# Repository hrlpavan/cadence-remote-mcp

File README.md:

#  Cadence-Remote-MCP: Prompt on Mac, Execute on Windows

> **Distributed AI Agent Infrastructure for Cadence Allegro X, OrCAD, and Heavy EDA Workloads via Model Context Protocol (MCP)**

<p align="center">
  
  <br>
  <em>Figure 1: 3D Photorealistic Isometric Render of the synthesized "HRL" Allegro X PCB layout (Glossy FR-4 substrate, gold ENIG chamfer, routed copper traces, and raised matte-white silkscreen).</em>
</p>

---

## 💡 The Problem & The Solution

Designing multi-layer printed circuit boards (PCBs) in enterprise hardware suites like **Cadence Allegro X** requires massive system resources: 50+ GB of disk space, dedicated NVIDIA GPUs, and 32–64 GB of RAM.

For engineers daily-driving portable setups like a **MacBook Air (M1/M2/M3)**:
- ❌ **Local Virtualization (Parallels/VMware)** divides limited unified memory, degrades battery, and consumes 120+ GB of local SSD space.
- ❌ **Native Windows Dual Boot** is impossible on Apple Silicon.

**Cadence-Remote-MCP solves this completely** by decoupling the **Orchestration Layer** from the **Execution Layer**:
- **Prompt on macOS**: Use Google Antigravity, Claude Desktop, or Cursor on your lightweight Mac.
- **Execute on Windows**: The physical workload runs on an external high-spec Windows workstation (Intel Core i9/i5 HX, RTX GPU, 32GB+ RAM) via remote MCP over secure HTTP/SSE.

---

## 🏛️ System Architecture

```
+───────────────────────────────────+                    +─────────────────────────────────────────+
│       MacBook Air (Client)        │                    │       Windows Workstation (Node)        │
├───────────────────────────────────┤                    ├─────────────────────────────────────────┤
│  [Google Antigravity / Cursor]    │   Remote HTTP      │   [winremote-mcp Server v4.1+]          │
│                │                  │   (SSE / JSON-RPC) │                 │                       │
│                ▼                  │                    │                 ▼                       │
│    Natural Language Prompts       ├───────────────────►│    Native PowerShell Shell Tools        │
│   "Route layer 3, print HRL..."   │  (Tunnel / LAN)    │    Cadence Allegro X CLI / SKILL Engine │
│                ▲                  │                    │    Real-Time Display / GPU Pipelines    │
│                │                  │                    │                 │                       │
│   Receives Live Screen & Logs     │◄───────────────────┤    Captured Window & DRC Telemetry      │
+───────────────────────────────────+                    +─────────────────────────────────────────+
```

---

## ✨ Key Features

- **Decoupled Architecture**: Prompt on macOS with zero fan noise; execute heavy Cadence calculations on a remote Windows workstation.
- **Full Tier 1–3 MCP Tooling (45+ Tools)**:
  - `Shell`: Execute PowerShell, batch scripts, and Cadence CLI (`allegro`, `extracta`, `dbdoctor`, `tclsh`).
  - `App`: Launch, focus, resize, and close Cadence Allegro X, OrCAD X, and System Capture.
  - `Snapshot` & `AnnotatedSnapshot`: Live visual feedback of the active PCB canvas streamed directly to your AI agent.
  - `FileRead` / `FileWrite` / `FileUpload` / `FileDownload`: Seamless two-way transfer of `.brd`, `.dsn`, gerbers, and SKILL scripts.
- **Zero-Config Network Traversal**:
  - Works over local Wi-Fi / Ethernet LAN.
  - Works over **Cloudflare Quick Tunnels** or **Tailscale** to effortlessly bypass strict router AP/Client Isolation (ideal for universities, offices, and coffee shops).
- **Hardened Security**: Protected with Bearer token authentication and isolated workspace drives (`D:\CadenceProjects`).

---

## 🏭 Industry & Enterprise Applications

1. **Hardware & Semiconductor Startups**:
   - Engineers can carry portable MacBooks for mobility while pooling expensive on-premise Windows workstation towers with dedicated licenses.
2. **Autonomous PCB Agent Pipelines**:
   - Integrate LLMs to inspect board layouts, run automated Design Rule Checks (DRC), and verify trace clearances programmatically via continuous agent loops.
3. **University Engineering Labs**:
   - Students can connect to shared department lab workstations without needing to install 60 GB EDA packages or configure complex VPNs.
4. **CI/CD Hardware Verification**:
   - Trigger remote board generation, layer Gerber exports, and impedance simulation checks as automated GitHub Actions / GitLab CI worker steps.

---

## 🚀 Quickstart Guide

### Step 1: Set Up the Windows Workstation (Execution Node)

1. Open **PowerShell** on your Windows workstation.
2. Clone or run our automated setup script:
   ```powershell
   # Install winremote-mcp
   python -m pip install winremote-mcp

   # Start the MCP server with authentication & full tool tier execution
   python -m winremote --host 0.0.0.0 --port 8090 --enable-all --auth-key "cadence-mcp-key"
   ```

3. **Expose the Endpoint** (If your local router blocks device-to-device Wi-Fi traffic):
   ```powershell
   # Run automated Cloudflare quick tunnel (0 accounts needed)
   winget install Cloudflare.cloudflared
   cloudflared tunnel --url http://127.0.0.1:8090
   ```
   *Note the generated public URL (e.g. `https://xxxx.trycloudflare.com`).*

---

### Step 2: Configure the Client (MacBook Air / Orchestrator)

Add the server to your agent MCP configuration:

#### For Google Antigravity (`~/.gemini/config/mcp_config.json`):
```json
{
  "mcpServers": {
    "cadence-worker": {
      "serverUrl": "https://xxxx.trycloudflare.com/mcp",
      "headers": {
        "Authorization": "Bearer cadence-mcp-key"
      }
    }
  }
}
```

#### For Claude Desktop (`claude_desktop_config.json`):
```json
{
  "mcpServers": {
    "cadence-worker": {
      "command": "npx",
      "args": [
        "-y",
        "mcp-remote@latest",
        "https://xxxx.trycloudflare.com/mcp",
        "--header",
        "Authorization: Bearer cadence-mcp-key"
      ]
    }
  }
}
```

---

## 🧪 Proof of Concept: The "HRL" Test Board

We validated the pipeline end-to-end by prompting from macOS to:
1. Initialize the remote session on a Windows 11 machine (`Intel Core i5-14450HX`).
2. Generate an isolated project directory (`D:\CadenceProjects\HRL_Test\`).
3. Synthesize a 2-layer FR-4 PCB layout with **`HRL`** silkscreen text and test headers.
4. Launch the preview in real-time on the Windows screen and stream a live camera snapshot back to macOS.
5. Render a **3D photorealistic isometric visualization** of the synthesized board with ray-traced ambient lighting, gold ENIG plating, and routed copper topologies.

---

## 👥 Contributors

This open-source project was created and engineered by:

- **[Pavan Kumar Sadashiv](https://github.com/hrlpavan)** — *Backend, AI Agent Systems & Infrastructure*
- **[Sugam](https://github.com)** — *Hardware & EDA Workflows Co-Creator*

---

## 📄 License

Distributed under the **MIT License**. See `LICENSE` for details.

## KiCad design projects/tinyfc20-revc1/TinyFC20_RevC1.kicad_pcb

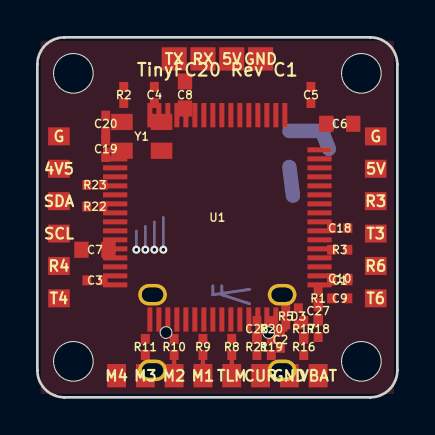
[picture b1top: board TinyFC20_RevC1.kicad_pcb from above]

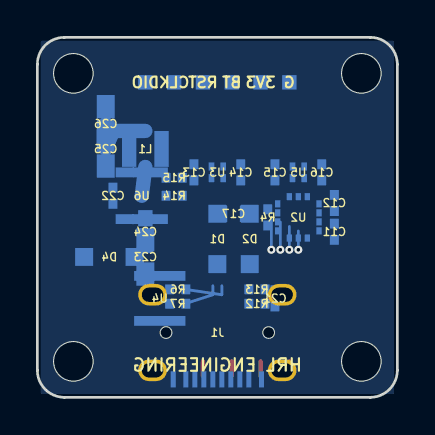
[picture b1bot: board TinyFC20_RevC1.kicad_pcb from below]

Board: 2 copper layers, 20.0 x 20.0 mm, 98 parts (36 on the bottom side), 3 nets.

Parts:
C1: 100 nF 16V X7R; 0402_C1
C2: 100 nF 16V X7R; 0402_C2
C3: 100 nF 16V X7R; 0402_C3
C4: 100 nF 16V X7R; 0402_C4
C5: 100 nF 16V X7R; 0402_C5
C6: 4.7 µF 10V X5R; 0603_C6
C7: 2.2 µF 10V X7R; 0603_C7
C8: 2.2 µF 10V X7R; 0603_C8
C9: 100 nF 16V X7R; 0402_C9
C10: 1.0 µF 10V X5R; 0402_C10
C11: 100 nF 16V X7R; 0402_C11
C12: 100 nF 16V X7R; 0402_C12
C13: 1.0 µF 10V X5R; 0402_C13
C14: 2.2 µF 16V X5R; 0402_C14
C15: 1.0 µF 10V X5R; 0402_C15
C16: 2.2 µF 16V X5R; 0402_C16
C17: 10 µF 10V X5R; 0603_C17
C18: 100 nF 16V X7R; 0402_C18
C19: 8.2 pF 50V C0G; 0402_C19
C20: 8.2 pF 50V C0G; 0402_C20
C21: 100 nF 16V X7R; 0402_C21
C22: 100 nF 16V X7R; 0402_C22
C23: 4.7 µF 50V X7R; 0805_C23
C24: 100 nF 50V X7R; 0603_C24
C25: 22 µF 16V X7R; 0805_C25
C26: 22 µF 16V X7R; 0805_C26
C27: 10 nF 16V X7R; 0402_C27
C28: 10 nF 16V X7R; 0402_C28
D1: MBR120VLSFT1G; SOD-123FL_D1
D2: MBR120VLSFT1G; SOD-123FL_D2
D3: APHHS1005CGCK; 0402_D3
D4: SMF26A; SOD-123FL_D4
H1, H2, H3, H4: MountingHole_2.2mm_M2
J1: USB4105-GF-A-060; USB4105_J1
L1: 4.7 µH; DFE252012F_L1
R1: 10 Ω; 0402_R1
R2: 10 kΩ; 0402_R2
R3: 10 kΩ; 0402_R3
R4: 10 kΩ; 0402_R4
R5: 1 kΩ; 0402_R5
R6: 22 Ω; 0402_R6
R7: 22 Ω; 0402_R7
R8: 33 Ω; 0402_R8
R9: 33 Ω; 0402_R9
R10: 33 Ω; 0402_R10
R11: 33 Ω; 0402_R11
R12: 5.1 kΩ 1%; 0402_R12
R13: 5.1 kΩ 1%; 0402_R13
R14: 53.6 kΩ 1%; 0402_R14
R15: 10.2 kΩ 1%; 0402_R15
R16: 150 kΩ 1%; 0402_R16
R17: 10.0 kΩ 1%; 0402_R17
R18: 1.00 kΩ 1%; 0402_R18
R19: 10.0 kΩ 1%; 0402_R19
R20: 10.0 kΩ 1%; 0402_R20
R21: 1.00 kΩ 1%; 0402_R21
R22: 4.70 kΩ 1%; 0402_R22
R23: 4.70 kΩ 1%; 0402_R23
TP1, TP2, TP3, TP4, TP5, TP6, TP7, TP8: TestPoint_Pad_1.05x1.3mm
TP9, TP10, TP11, TP12: TestPoint_Pad_1.4x1.3mm
TP13, TP14, TP15, TP16, TP17, TP18, TP19, TP20, TP21, TP22, TP23, TP24: TestPoint_Pad_1.2x1.0mm
TP25, TP26, TP27, TP28, TP29, TP30: TestPoint_Pad_0.8x0.8mm
U1: STM32F405RGT6; LQFP-64_U1
U2: LSM6DSOTR; LGA-14_U2
U3: LP5907SNX-3.3/NOPB; X2SON-4_U3
U4: USBLC6-2SC6; SOT-23-6_U4
U5: LP5907SNX-3.3/NOPB; X2SON-4_U5
U6: LMR51625YDDCR; TSOT-23-6_U6
Y1: 8 MHz 8pF; SMD-3225_Y1

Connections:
5V_BEC: TP11.1, TP23.1
+3V3: C1.2, C2.2, C3.2, C4.2, C5.2, C9.2, C10.2, C11.2, C12.2, C13.2, C14.2, C15.2, C16.2, C18.2, C19.2, C20.2, C21.2, C22.2, C27.2, C28.2, D3.2, R1.2, R2.2, R3.2, R4.2, R5.2, R6.2, R7.2, R8.2, R9.2, R10.2, R11.2, R12.2, R13.2, R14.2, R15.2, R16.2, R17.2, R18.2, R19.2, R20.2, R21.2, R22.2, R23.2, TP29.1
GND: C1.1, C2.1, C3.1, C4.1, C5.1, C9.1, C10.1, C11.1, C12.1, C13.1, C14.1, C15.1, C16.1, C18.1, C19.1, C20.1, C21.1, C22.1, C27.1, C28.1, D3.1, R1.1, R2.1, R3.1, R4.1, R5.1, R6.1, R7.1, R8.1, R9.1, R10.1, R11.1, R12.1, R13.1, R14.1, R15.1, R16.1, R17.1, R18.1, R19.1, R20.1, R21.1, R22.1, R23.1, TP7.1, TP12.1, TP18.1, TP24.1, TP30.1

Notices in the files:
README.md:
License: MIT
